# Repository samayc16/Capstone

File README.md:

# Code Documentation for Full STEAM Ahead
### Samay Chandna

#### Useful Links
* [micro:bit API for TS](https://makecode.microbit.org/reference)
* [micro:bit Pinout](https://makecode.microbit.org/device/pins)
* [micro:bit Progress with Simulator](https://makecode.microbit.org/_6Y6azqKkKF0U)

#### Progress Made so far
* 26/09/2023
  * [Have skeleton working in block code](https://makecode.microbit.org/_6Y6azqKkKF0U)
  * 
* 28/09/2023
  * [Moved from naive implementation to I2C](https://makecode.microbit.org/S04872-52139-73553-07116)
  * 
  * 
* 24/10/2023
  * Little bit of absence due to midterms, break, and interviews
  * Great progress made, all the block code looks production-ready
  * 
  * 
  * Deleted all deprecated python code
  * Deleted all TS files that are not being used
  * Got rid of custom.ts, made seperate modules for each (makes MUCH more sense)
  * Added PCB to github repo
  * Added my parts of CDR document and presentation

#### Helpful Notes

*"\uf000", "id": "fa-glass"

*"\uf001", "id": "fa-music"

*"\uf002", "id": "fa-search"

*"\uf003", "id": "fa-envelope-o"

*"\uf004", "id": "fa-heart"

*"\uf005", "id": "fa-star"

*"\uf006", "id": "fa-star-o"

*"\uf007", "id": "fa-user"

*"\uf008", "id": "fa-film"

*"\uf009", "id": "fa-th-large"

*"\uf00a", "id": "fa-th"

*"\uf00b", "id": "fa-th-list"

*"\uf00c", "id": "fa-check"

*"\uf00d", "id": "fa-times"

*"\uf00e", "id": "fa-search-plus"

*"\uf010", "id": "fa-search-minus"

*"\uf011", "id": "fa-power-off"

*"\uf012", "id": "fa-signal"

*"\uf013", "id": "fa-cog"

*"\uf014", "id": "fa-trash-o"

*"\uf015", "id": "fa-home"

*"\uf016", "id": "fa-file-o"

*"\uf017", "id": "fa-clock-o"

*"\uf018", "id": "fa-road"

*"\uf019", "id": "fa-download"

*"\uf01a", "id": "fa-arrow-circle-o-down"

*"\uf01b", "id": "fa-arrow-circle-o-up"

*"\uf01c", "id": "fa-inbox"

*"\uf01d", "id": "fa-play-circle-o"

*"\uf01e", "id": "fa-repeat"

*"\uf021", "id": "fa-refresh"

*"\uf022", "id": "fa-list-alt"

*"\uf023", "id": "fa-lock"

*"\uf024", "id": "fa-flag"

*"\uf025", "id": "fa-headphones"

*"\uf026", "id": "fa-volume-off"

*"\uf027", "id": "fa-volume-down"

*"\uf028", "id": "fa-volume-up"

*"\uf029", "id": "fa-qrcode"

*"\uf02a", "id": "fa-barcode"

*"\uf02b", "id": "fa-tag"

*"\uf02c", "id": "fa-tags"

*"\uf02d", "id": "fa-book"

*"\uf02e", "id": "fa-bookmark"

*"\uf02f", "id": "fa-print"

*"\uf030", "id": "fa-camera"

*"\uf031", "id": "fa-font"

*"\uf032", "id": "fa-bold"

*"\uf033", "id": "fa-italic"

*"\uf034", "id": "fa-text-height"

*"\uf035", "id": "fa-text-width"

*"\uf036", "id": "fa-align-left"

*"\uf037", "id": "fa-align-center"

*"\uf038", "id": "fa-align-right"

*"\uf039", "id": "fa-align-justify"

*"\uf03a", "id": "fa-list"

*"\uf03b", "id": "fa-outdent"

*"\uf03c", "id": "fa-indent"

*"\uf03d", "id": "fa-video-camera"

*"\uf03e", "id": "fa-picture-o"

*"\uf040", "id": "fa-pencil"

*"\uf041", "id": "fa-map-marker"

*"\uf042", "id": "fa-adjust"

*"\uf043", "id": "fa-tint"

*"\uf044", "id": "fa-pencil-square-o"

*"\uf045", "id": "fa-share-square-o"

*"\uf046", "id": "fa-check-square-o"

*"\uf047", "id": "fa-arrows"

*"\uf048", "id": "fa-step-backward"

*"\uf049", "id": "fa-fast-backward"

*"\uf04a", "id": "fa-backward"

*"\uf04b", "id": "fa-play"

*"\uf04c", "id": "fa-pause"

*"\uf04d", "id": "fa-stop"

*"\uf04e", "id": "fa-forward"

*"\uf050", "id": "fa-fast-forward"

*"\uf051", "id": "fa-step-forward"

*"\uf052", "id": "fa-eject"

*"\uf053", "id": "fa-chevron-left"

*"\uf054", "id": "fa-chevron-right"

*"\uf055", "id": "fa-plus-circle"

*"\uf056", "id": "fa-minus-circle"

*"\uf057", "id": "fa-times-circle"

*"\uf058", "id": "fa-check-circle"

*"\uf059", "id": "fa-question-circle"

*"\uf05a", "id": "fa-info-circle"

*"\uf05b", "id": "fa-crosshairs"

*"\uf05c", "id": "fa-times-circle-o"

*"\uf05d", "id": "fa-check-circle-o"

*"\uf05e", "id": "fa-ban"

*"\uf060", "id": "fa-arrow-left"

*"\uf061", "id": "fa-arrow-right"

*"\uf062", "id": "fa-arrow-up"

*"\uf063", "id": "fa-arrow-down"

*"\uf064", "id": "fa-share"

*"\uf065", "id": "fa-expand"

*"\uf066", "id": "fa-compress"

*"\uf067", "id": "fa-plus"

*"\uf068", "id": "fa-minus"

*"\uf069", "id": "fa-asterisk"

*"\uf06a", "id": "fa-exclamation-circle"

*"\uf06b", "id": "fa-gift"

*"\uf06c", "id": "fa-leaf"

*"\uf06d", "id": "fa-fire"

*"\uf06e", "id": "fa-eye"

*"\uf070", "id": "fa-eye-slash"

*"\uf071", "id": "fa-exclamation-triangle"

*"\uf072", "id": "fa-plane"

*"\uf073", "id": "fa-calendar"

*"\uf074", "id": "fa-random"

*"\uf075", "id": "fa-comment"

*"\uf076", "id": "fa-magnet"

*"\uf077", "id": "fa-chevron-up"

*"\uf078", "id": "fa-chevron-down"

*"\uf079", "id": "fa-retweet"

*"\uf07a", "id": "fa-shopping-cart"

*"\uf07b", "id": "fa-folder"

*"\uf07c", "id": "fa-folder-open"

*"\uf07d", "id": "fa-arrows-v"

*"\uf07e", "id": "fa-arrows-h"

*"\uf080", "id": "fa-bar-chart-o"

*"\uf081", "id": "fa-twitter-square"

*"\uf082", "id": "fa-facebook-square"

*"\uf083", "id": "fa-camera-retro"

*"\uf084", "id": "fa-key"

*"\uf085", "id": "fa-cogs"

*"\uf086", "id": "fa-comments"

*"\uf087", "id": "fa-thumbs-o-up"

*"\uf088", "id": "fa-thumbs-o-down"

*"\uf089", "id": "fa-star-half"

*"\uf08a", "id": "fa-heart-o"

*"\uf08b", "id": "fa-sign-out"

*"\uf08c", "id": "fa-linkedin-square"

*"\uf08d", "id": "fa-thumb-tack"

*"\uf08e", "id": "fa-external-link"

*"\uf090", "id": "fa-sign-in"

*"\uf091", "id": "fa-trophy"

*"\uf092", "id": "fa-github-square"

*"\uf093", "id": "fa-upload"

*"\uf094", "id": "fa-lemon-o"

*"\uf095", "id": "fa-phone"

*"\uf096", "id": "fa-square-o"

*"\uf097", "id": "fa-bookmark-o"

*"\uf098", "id": "fa-phone-square"

*"\uf099", "id": "fa-twitter"

*"\uf09a", "id": "fa-facebook"

*"\uf09b", "id": "fa-github"

*"\uf09c", "id": "fa-unlock"

*"\uf09d", "id": "fa-credit-card"

*"\uf09e", "id": "fa-rss"

*"\uf0a0", "id": "fa-hdd-o"

*"\uf0a1", "id": "fa-bullhorn"

*"\uf0f3", "id": "fa-bell"

*"\uf0a3", "id": "fa-certificate"

*"\uf0a4", "id": "fa-hand-o-right"

*"\uf0a5", "id": "fa-hand-o-left"

*"\uf0a6", "id": "fa-hand-o-up"

*"\uf0a7", "id": "fa-hand-o-down"

*"\uf0a8", "id": "fa-arrow-circle-left"

*"\uf0a9", "id": "fa-arrow-circle-right"

*"\uf0aa", "id": "fa-arrow-circle-up"

*"\uf0ab", "id": "fa-arrow-circle-down"

*"\uf0ac", "id": "fa-globe"

*"\uf0ad", "id": "fa-wrench"

*"\uf0ae", "id": "fa-tasks"

*"\uf0b0", "id": "fa-filter"

*"\uf0b1", "id": "fa-briefcase"

*"\uf0b2", "id": "fa-arrows-alt"

*"\uf0c0", "id": "fa-users"

*"\uf0c1", "id": "fa-link"

*"\uf0c2", "id": "fa-cloud"

*"\uf0c3", "id": "fa-flask"

*"\uf0c4", "id": "fa-scissors"

*"\uf0c5", "id": "fa-files-o"

*"\uf0c6", "id": "fa-paperclip"

*"\uf0c7", "id": "fa-floppy-o"

*"\uf0c8", "id": "fa-square"

*"\uf0c9", "id": "fa-bars"

*"\uf0ca", "id": "fa-list-ul"

*"\uf0cb", "id": "fa-list-ol"

*"\uf0cc", "id": "fa-strikethrough"

*"\uf0cd", "id": "fa-underline"

*"\uf0ce", "id": "fa-table"

*"\uf0d0", "id": "fa-magic"

*"\uf0d1", "id": "fa-truck"

*"\uf0d2", "id": "fa-pinterest"

*"\uf0d3", "id": "fa-pinterest-square"

*"\uf0d4", "id": "fa-google-plus-square"

*"\uf0d5", "id": "fa-google-plus"

*"\uf0d6", "id": "fa-money"

*"\uf0d7", "id": "fa-caret-down"

*"\uf0d8", "id": "fa-caret-up"

*"\uf0d9", "id": "fa-caret-left"

*"\uf0da", "id": "fa-caret-right"

*"\uf0db", "id": "fa-columns"

*"\uf0dc", "id": "fa-sort"

*"\uf0dd", "id": "fa-sort-asc"

*"\uf0de", "id": "fa-sort-desc"

*"\uf0e0", "id": "fa-envelope"

*"\uf0e1", "id": "fa-linkedin"

*"\uf0e2", "id": "fa-undo"

*"\uf0e3", "id": "fa-gavel"

*"\uf0e4", "id": "fa-tachometer"

*"\uf0e5", "id": "fa-comment-o"

*"\uf0e6", "id": "fa-comments-o"

*"\uf0e7", "id": "fa-bolt"

*"\uf0e8", "id": "fa-sitemap"

*"\uf0e9", "id": "fa-umbrella"

*"\uf0ea", "id": "fa-clipboard"

*"\uf0eb", "id": "fa-lightbulb-o"

*"\uf0ec", "id": "fa-exchange"

*"\uf0ed", "id": "fa-cloud-download"

*"\uf0ee", "id": "fa-cloud-upload"

*"\uf0f0", "id": "fa-user-md"

*"\uf0f1", "id": "fa-stethoscope"

*"\uf0f2", "id": "fa-suitcase"

*"\uf0a2", "id": "fa-bell-o"

*"\uf0f4", "id": "fa-coffee"

*"\uf0f5", "id": "fa-cutlery"

*"\uf0f6", "id": "fa-file-text-o"

*"\uf0f7", "id": "fa-building-o"

*"\uf0f8", "id": "fa-hospital-o"

*"\uf0f9", "id": "fa-ambulance"

*"\uf0fa", "id": "fa-medkit"

*"\uf0fb", "id": "fa-fighter-jet"

*"\uf0fc", "id": "fa-beer"

*"\uf0fd", "id": "fa-h-square"

*"\uf0fe", "id": "fa-plus-square"

*"\uf100", "id": "fa-angle-double-left"

*"\uf101", "id": "fa-angle-double-right"

*"\uf102", "id": "fa-angle-double-up"

*"\uf103", "id": "fa-angle-double-down"

*"\uf104", "id": "fa-angle-left"

*"\uf105", "id": "fa-angle-right"

*"\uf106", "id": "fa-angle-up"

*"\uf107", "id": "fa-angle-down"

*"\uf108", "id": "fa-desktop"

*"\uf109", "id": "fa-laptop"

*"\uf10a", "id": "fa-tablet"

*"\uf10b", "id": "fa-mobile"

*"\uf10c", "id": "fa-circle-o"

*"\uf10d", "id": "fa-quote-left"

*"\uf10e", "id": "fa-quote-right"

*"\uf110", "id": "fa-spinner"

*"\uf111", "id": "fa-circle"

*"\uf112", "id": "fa-reply"

*"\uf113", "id": "fa-github-alt"

*"\uf114", "id": "fa-folder-o"

*"\uf115", "id": "fa-folder-open-o"

*"\uf118", "id": "fa-smile-o"

*"\uf119", "id": "fa-frown-o"

*"\uf11a", "id": "fa-meh-o"

*"\uf11b", "id": "fa-gamepad"

*"\uf11c", "id": "fa-keyboard-o"

*"\uf11d", "id": "fa-flag-o"

*"\uf11e", "id": "fa-flag-checkered"

*"\uf120", "id": "fa-terminal"

*"\uf121", "id": "fa-code"

*"\uf122", "id": "fa-reply-all"

*"\uf122", "id": "fa-mail-reply-all"

*"\uf123", "id": "fa-star-half-o"

*"\uf124", "id": "fa-location-arrow"

*"\uf125", "id": "fa-crop"

*"\uf126", "id": "fa-code-fork"

*"\uf127", "id": "fa-chain-broken"

*"\uf128", "id": "fa-question"

*"\uf129", "id": "fa-info"

*"\uf12a", "id": "fa-exclamation"

*"\uf12b", "id": "fa-superscript"

*"\uf12c", "id": "fa-subscript"

*"\uf12d", "id": "fa-eraser"

*"\uf12e", "id": "fa-puzzle-piece"

*"\uf130", "id": "fa-microphone"

*"\uf131", "id": "fa-microphone-slash"

*"\uf132", "id": "fa-shield"

*"\uf133", "id": "fa-calendar-o"

*"\uf134", "id": "fa-fire-extinguisher"

*"\uf135", "id": "fa-rocket"

*"\uf136", "id": "fa-maxcdn"

*"\uf137", "id": "fa-chevron-circle-left"

*"\uf138", "id": "fa-chevron-circle-right"

*"\uf139", "id": "fa-chevron-circle-up"

*"\uf13a", "id": "fa-chevron-circle-down"

*"\uf13b", "id": "fa-html5"

*"\uf13c", "id": "fa-css3"

*"\uf13d", "id": "fa-anchor"

*"\uf13e", "id": "fa-unlock-alt"

*"\uf140", "id": "fa-bullseye"

*"\uf141", "id": "fa-ellipsis-h"

*"\uf142", "id": "fa-ellipsis-v"

*"\uf143", "id": "fa-rss-square"

*"\uf144", "id": "fa-play-circle"

*"\uf145", "id": "fa-ticket"

*"\uf146", "id": "fa-minus-square"

*"\uf147", "id": "fa-minus-square-o"

*"\uf148", "id": "fa-level-up"

*"\uf149", "id": "fa-level-down"

*"\uf14a", "id": "fa-check-square"

*"\uf14b", "id": "fa-pencil-square"

*"\uf14c", "id": "fa-external-link-square"

*"\uf14d", "id": "fa-share-square"

*"\uf14e", "id": "fa-compass"

*"\uf150", "id": "fa-caret-square-o-down"

*"\uf151", "id": "fa-caret-square-o-up"

*"\uf152", "id": "fa-caret-square-o-right"

*"\uf153", "id": "fa-eur"

*"\uf154", "id": "fa-gbp"

*"\uf155", "id": "fa-usd"

*"\uf156", "id": "fa-inr"

*"\uf157", "id": "fa-jpy"

*"\uf158", "id": "fa-rub"

*"\uf159", "id": "fa-krw"

*"\uf15a", "id": "fa-btc"

*"\uf15b", "id": "fa-file"

*"\uf15c", "id": "fa-file-text"

*"\uf15d", "id": "fa-sort-alpha-asc"

*"\uf15e", "id": "fa-sort-alpha-desc"

*"\uf160", "id": "fa-sort-amount-asc"

*"\uf161", "id": "fa-sort-amount-desc"

*"\uf162", "id": "fa-sort-numeric-asc"

*"\uf163", "id": "fa-sort-numeric-desc"

*"\uf164", "id": "fa-thumbs-up"

*"\uf165", "id": "fa-thumbs-down"

*"\uf166", "id": "fa-youtube-square"

*"\uf167", "id": "fa-youtube"

*"\uf168", "id": "fa-xing"

*"\uf169", "id": "fa-xing-square"

*"\uf16a", "id": "fa-youtube-play"

*"\uf16b", "id": "fa-dropbox"

*"\uf16c", "id": "fa-stack-overflow"

*"\uf16d", "id": "fa-instagram"

*"\uf16e", "id": "fa-flickr"

*"\uf170", "id": "fa-adn"

*"\uf171", "id": "fa-bitbucket"

*"\uf172", "id": "fa-bitbucket-square"

*"\uf173", "id": "fa-tumblr"

*"\uf174", "id": "fa-tumblr-square"

*"\uf175", "id": "fa-long-arrow-down"

*"\uf176", "id": "fa-long-arrow-up"

*"\uf177", "id": "fa-long-arrow-left"

*"\uf178", "id": "fa-long-arrow-right"

*"\uf179", "id": "fa-apple"

*"\uf17a", "id": "fa-windows"

*"\uf17b", "id": "fa-android"

*"\uf17c", "id": "fa-linux"

*"\uf17d", "id": "fa-dribbble"

*"\uf17e", "id": "fa-skype"

*"\uf180", "id": "fa-foursquare"

*"\uf181", "id": "fa-trello"

*"\uf182", "id": "fa-female"

*"\uf183", "id": "fa-male"

*"\uf184", "id": "fa-gittip"

*"\uf185", "id": "fa-sun-o"

*"\uf186", "id": "fa-moon-o"

*"\uf187", "id": "fa-archive"

*"\uf188", "id": "fa-bug"

*"\uf189", "id": "fa-vk"

*"\uf18a", "id": "fa-weibo"

*"\uf18b", "id": "fa-renren"

*"\uf18c", "id": "fa-pagelines"

*"\uf18d", "id": "fa-stack-exchange"

*"\uf18e", "id": "fa-arrow-circle-o-right"

*"\uf190", "id": "fa-arrow-circle-o-left"

*"\uf191", "id": "fa-caret-square-o-left"

*"\uf192", "id": "fa-dot-circle-o"

*"\uf193", "id": "fa-wheelchair"

*"\uf194", "id": "fa-vimeo-square"

*"\uf195", "id": "fa-try"

*"\uf196", "id": "fa-plus-square-o")

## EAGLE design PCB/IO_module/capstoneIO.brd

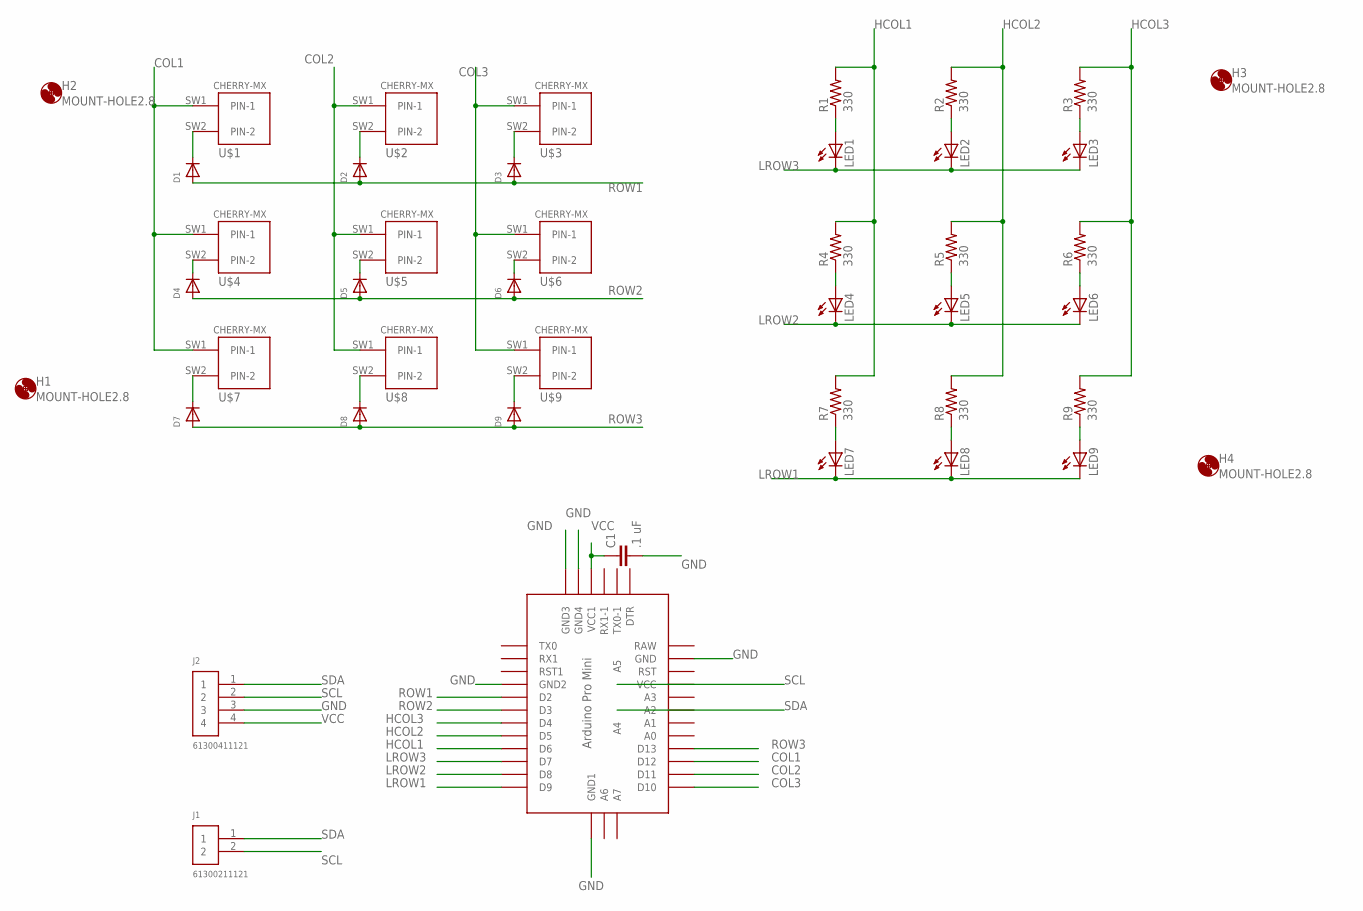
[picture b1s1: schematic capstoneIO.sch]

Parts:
C1: .1 uF; C075-032X103-AARON
D1, D2, D3, D4, D5, D6, D7, D8, D9: DIODEDO-1N4148; DO-1N4148
H1, H2, H3, H4: MOUNT-HOLE2.8; 2,8
J1: 61300211121
J2: 61300411121
LED1, LED2, LED3, LED4, LED5, LED6, LED7, LED8, LED9: LED5MM
R1, R2, R3, R4, R5, R6, R7, R8, R9: 330; 0204/7
U$1, U$2, U$3, U$4, U$5, U$6, U$7, U$8, U$9: CHERRY-MX
U$10: ABK-PRO-MINI

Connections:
COL1: U$1.SW1 (PIN-1), U$4.SW1 (PIN-1), U$7.SW1 (PIN-1), U$10.D12
COL2: U$2.SW1 (PIN-1), U$5.SW1 (PIN-1), U$8.SW1 (PIN-1), U$10.D11
COL3: U$3.SW1 (PIN-1), U$6.SW1 (PIN-1), U$9.SW1 (PIN-1), U$10.D10
GND: C1.2, J2.3, U$10.GND, U$10.GND1 (GND2), U$10.GND2 (GND3), U$10.GND3 (GND4), U$10.GND4 (GND1)
HCOL1: R1.2, R4.2, R7.2, U$10.D6
HCOL2: R2.2, R5.2, R8.2, U$10.D5
HCOL3: R3.2, R6.2, R9.2, U$10.D4
LROW1: LED7.K (C), LED8.K (C), LED9.K (C), U$10.D9
LROW2: LED4.K (C), LED5.K (C), LED6.K (C), U$10.D8
LROW3: LED1.K (C), LED2.K (C), LED3.K (C), U$10.D7
unnamed: LED1.A, R1.1
unnamed: LED2.A, R2.1
unnamed: LED3.A, R3.1
unnamed: D1.C, U$1.SW2 (PIN-2)
unnamed: LED4.A, R4.1
unnamed: D3.C, U$3.SW2 (PIN-2)
unnamed: D2.C, U$2.SW2 (PIN-2)
unnamed: D4.C, U$4.SW2 (PIN-2)
unnamed: D5.C, U$5.SW2 (PIN-2)
unnamed: D6.C, U$6.SW2 (PIN-2)
unnamed: LED5.A, R5.1
unnamed: D7.C, U$7.SW2 (PIN-2)
unnamed: D8.C, U$8.SW2 (PIN-2)
unnamed: D9.C, U$9.SW2 (PIN-2)
unnamed: LED6.A, R6.1
unnamed: LED7.A, R7.1
unnamed: LED8.A, R8.1
unnamed: LED9.A, R9.1
ROW1: D1.A, D2.A, D3.A, U$10.D2
ROW2: D4.A, D5.A, D6.A, U$10.D3
ROW3: D7.A, D8.A, D9.A, U$10.D13
SCL: J1.2, J2.2, U$10.A5
SDA: J1.1, J2.1, U$10.A4
VCC: C1.1, J2.4, U$10.VCC1

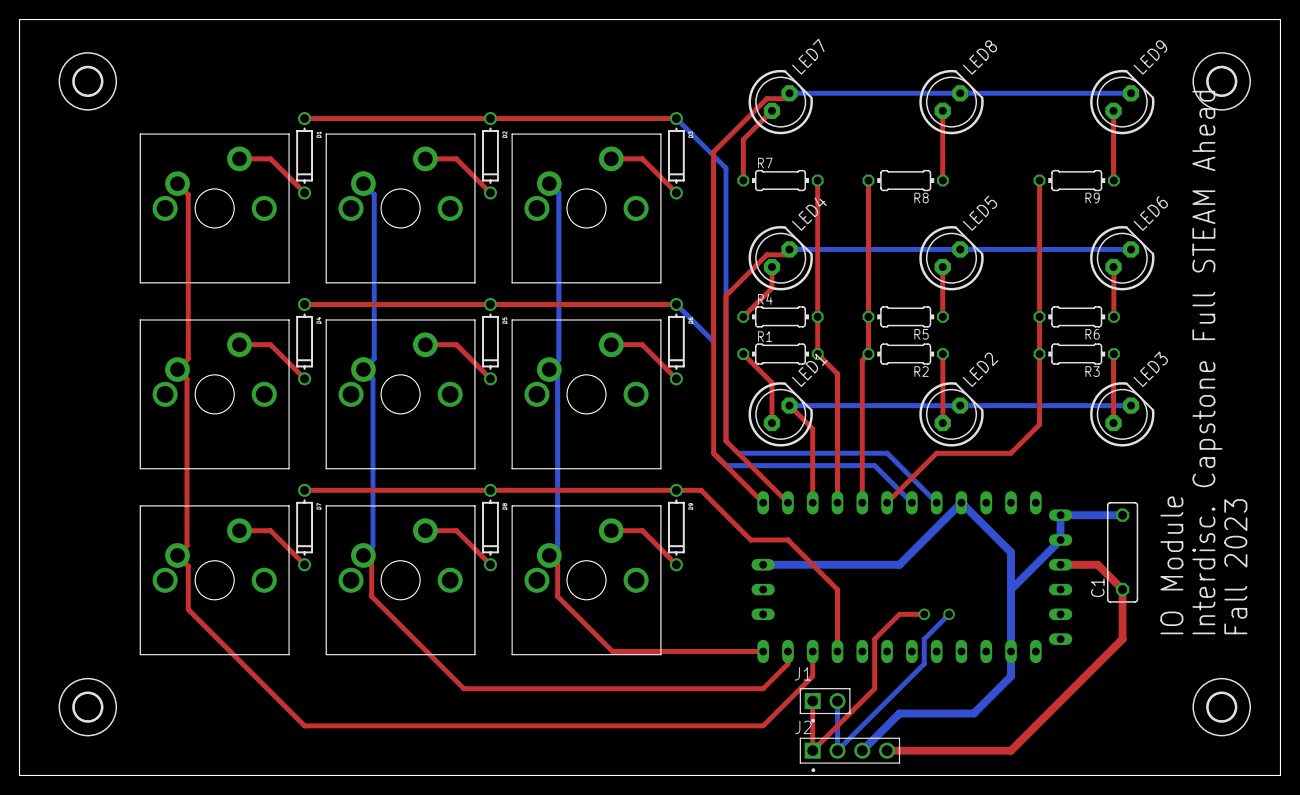
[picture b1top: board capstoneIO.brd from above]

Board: 2 copper layers, 129.2 x 77.5 mm, 44 parts (0 on the bottom side), 34 nets.

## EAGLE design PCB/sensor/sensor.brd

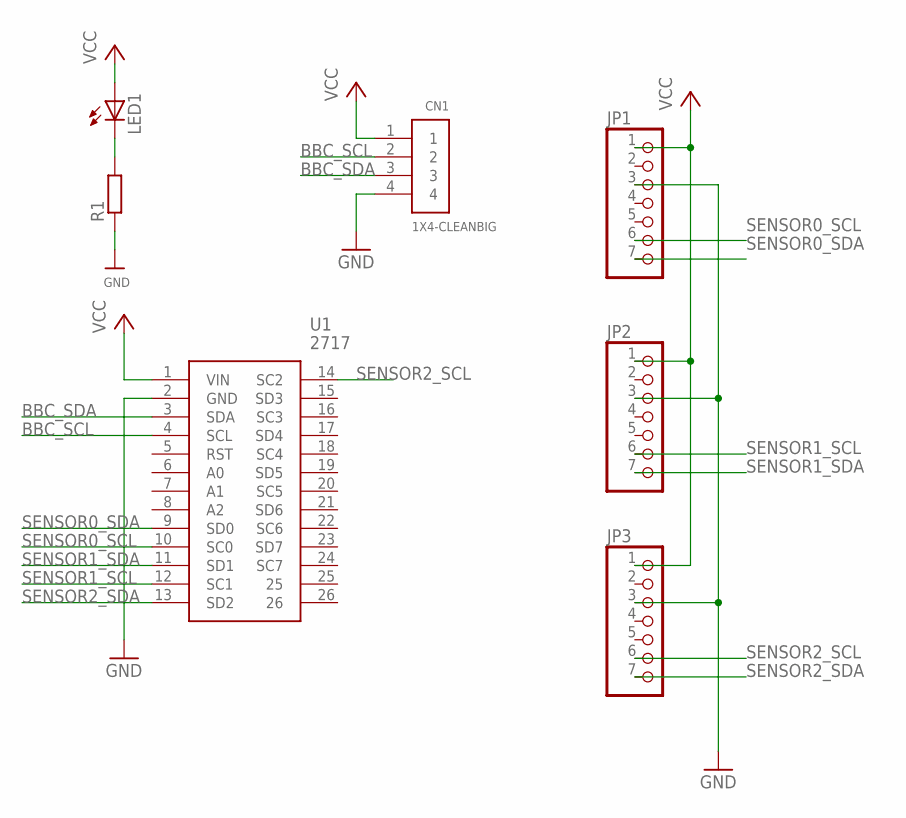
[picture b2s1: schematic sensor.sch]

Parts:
CN1: 1X4-CLEANBIG; 1X04-CLEANBIG
JP1, JP2, JP3: MICROBUILDER_HEADER-1X7; MICROBUILDER_1X07_OVAL
LED1: LED3MM
R1: R-EU_0204/7; 0204/7
U1: 2717

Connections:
BBC_SCL: CN1.2, U1.4 (SCL)
BBC_SDA: CN1.3, U1.3 (SDA)
GND: CN1.4, JP1.3, JP2.3, JP3.3, R1.1, U1.2 (GND)
unnamed: LED1.K (C), R1.2
SENSOR0_SCL: JP1.6, U1.10 (SC0)
SENSOR0_SDA: JP1.7, U1.9 (SD0)
SENSOR1_SCL: JP2.6, U1.12 (SC1)
SENSOR1_SDA: JP2.7, U1.11 (SD1)
SENSOR2_SCL: JP3.6, U1.14 (SC2)
SENSOR2_SDA: JP3.7, U1.13 (SD2)
VCC: CN1.1, JP1.1, JP2.1, JP3.1, LED1.A, U1.1 (VIN)

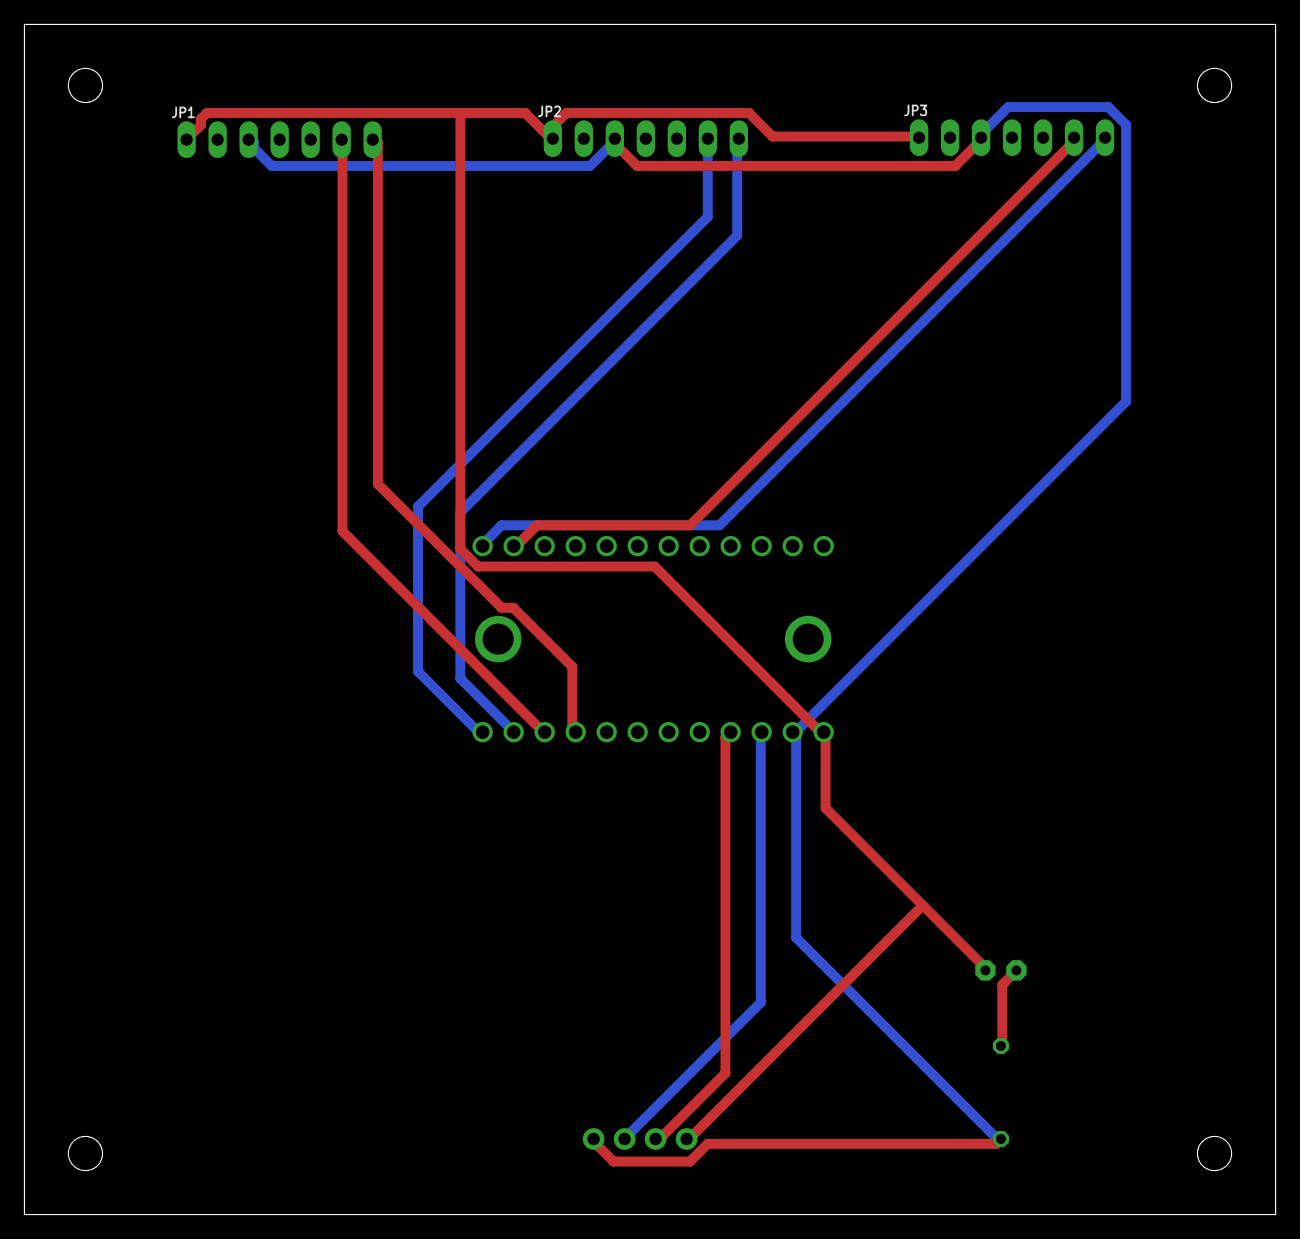
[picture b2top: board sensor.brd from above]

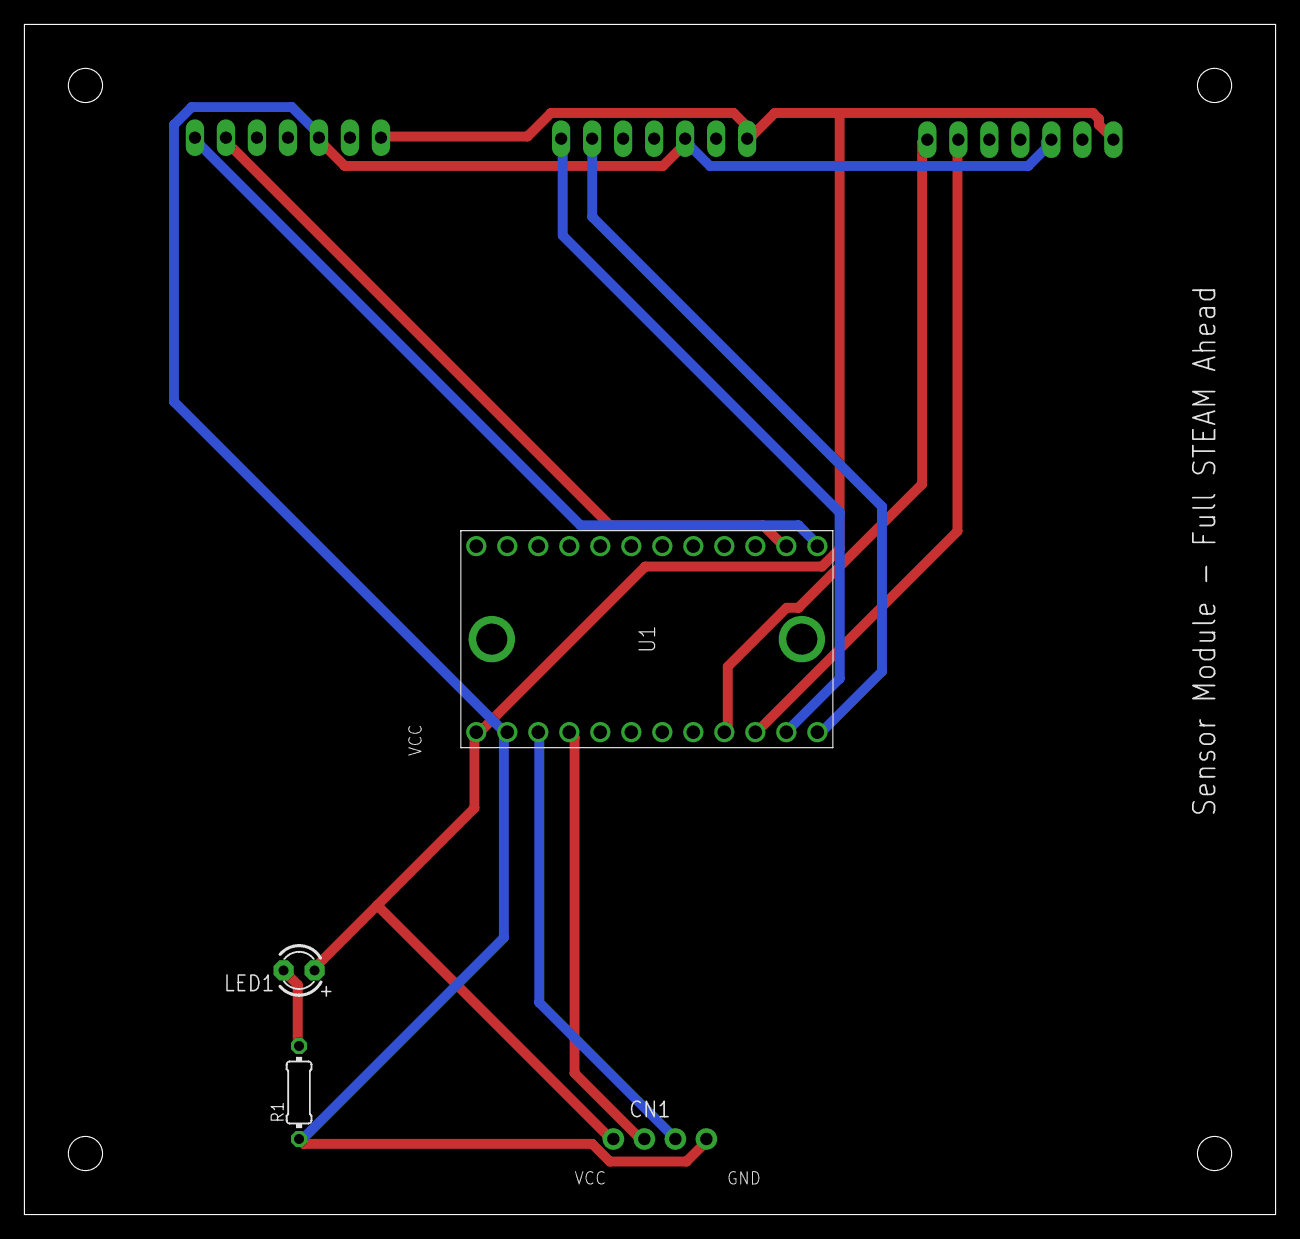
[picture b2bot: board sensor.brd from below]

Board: 2 copper layers, 102.5 x 97.5 mm, 7 parts (4 on the bottom side), 11 nets.

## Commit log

2023-09-24 Initialize repo added README.md
2023-09-24 Added microBit Class
2023-09-25 removed python code, moving to TS (makes life much simpler)
2023-09-25 created base class: - microBit created extensions of microBit: - mainBody - appendageParent created children of appendageParent: - karaokeAppendage - displayAppendage - wheelAppendage - musicBlockApp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
    - allows for coding on vscode locally
    - also compiles locally
    mainBody:
    - has logic to determine which module is connected where
    - has logic to send/receive serially via RX/TX lines
    appendageParent
2023-09-25 mend
2023-09-25 created base class: - microBit created extensions of microBit: - mainBody - appendageParent created children of appendageParent: - karaokeAppendage - displayAppendage - wheelAppendage - musicBlockApp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
    - allows for coding on vscode locally
    - also compiles locally
    mainBody:
    - has logic to determine which module is connected where
    - has logic to send/receive serially via RX/TX lines
    appendageParent
2023-09-26 Created helper functions to make code readable Changed pins to guarantee support of serial RxTx & appendageID
2023-09-26 minor changes
2023-09-26 created blocks for functions updated README
2023-09-28 Changed connections from naive solution to I2C
    Created 'real' block functions with documentation
2023-10-24 added music block module and updated readme
2023-10-24 removed custom, created file for each module
    added more useful notes to readme
2023-11-01 Arrpegiates on connected music blocks
2023-11-01 Use mcirobit gamepad to move
2023-11-17 removed karaoke module, added button io module
2023-12-12 Addition of Motor CAD and code to repository
